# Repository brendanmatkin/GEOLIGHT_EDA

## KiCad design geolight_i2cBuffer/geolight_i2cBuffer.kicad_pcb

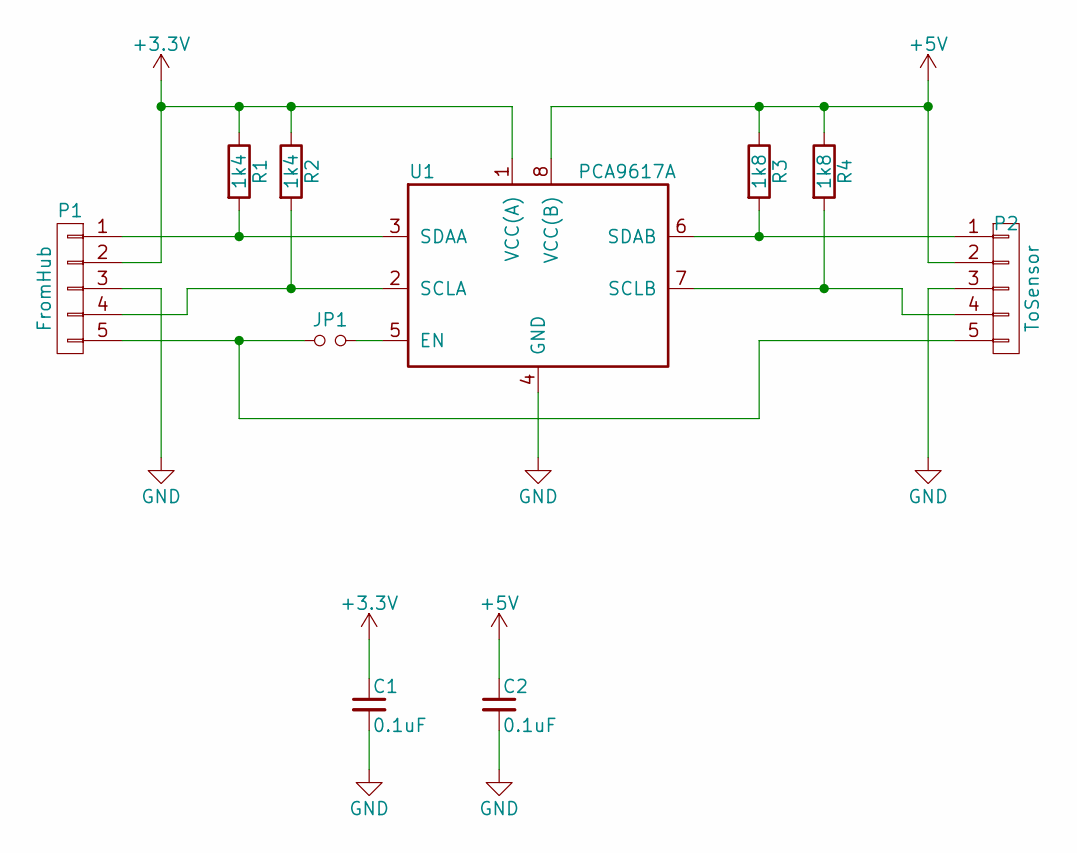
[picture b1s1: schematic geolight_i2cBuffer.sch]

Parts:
C1, C2: 0.1uF; C_Disc_D3_P2.5
JP1: Jumper_NO_Small; GS2
P1: FromHub; Pin_Header_Straight_1x05
P2: ToSensor; Socket_Strip_Straight_1x05
R1, R2: 1k4; R4
R3, R4: 1k8; R4
U1: PCA9617A; TSSOP-8_3x3mm_Pitch0.65mm

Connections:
+3V3: C1.1, P1.2, R1.1, R2.1, U1.1 (VCC(A))
+5V: C2.1, P2.2, R3.1, R4.1, U1.8 (VCC(B))
GND: C1.2, C2.2, P1.3, P2.3, U1.4 (GND)
unnamed 3: JP1.1, P1.5, P2.5; also elsewhere on the board
unnamed 4: JP1.2, U1.5 (EN); also elsewhere on the board
unnamed: P1.1, R1.2, U1.3 (SDAA)
unnamed: P1.4, R2.2, U1.2 (SCLA)
unnamed: P2.1, R3.2, U1.6 (SDAB)
unnamed: P2.4, R4.2, U1.7 (SCLB)

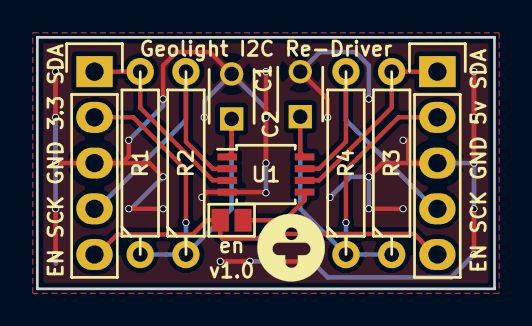
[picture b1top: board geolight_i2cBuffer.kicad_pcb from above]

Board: 2 copper layers, 25.4 x 14.0 mm, 10 parts (0 on the bottom side), 9 nets.

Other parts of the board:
en: Jumper_NO_Small; GS2

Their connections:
unnamed 3: en.1; also elsewhere on the board
unnamed 4: en.2; also elsewhere on the board

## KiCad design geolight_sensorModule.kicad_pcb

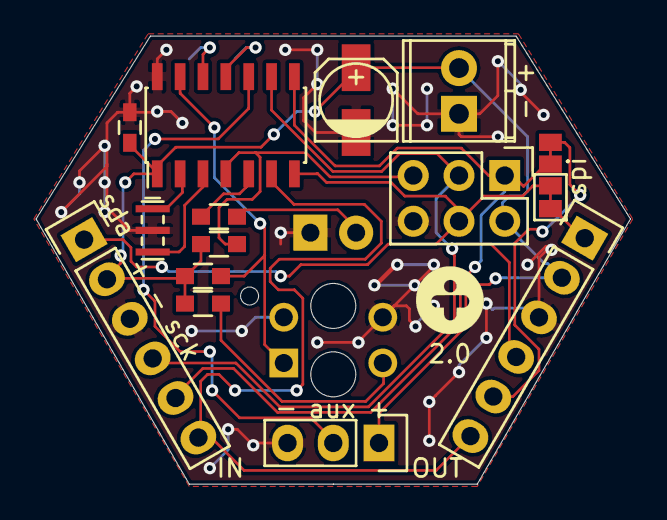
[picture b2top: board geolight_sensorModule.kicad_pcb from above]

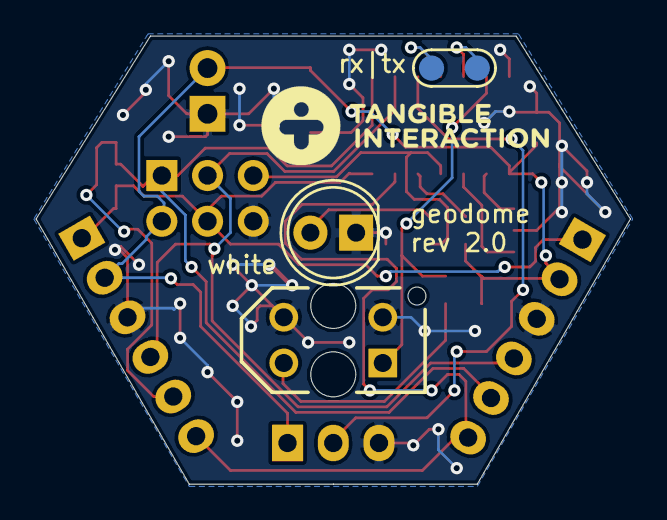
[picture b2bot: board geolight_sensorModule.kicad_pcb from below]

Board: 2 copper layers, 33.0 x 24.9 mm, 19 parts (3 on the bottom side), 16 nets.

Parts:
C2: 0.1uF; C_0603_HandSolderingShort
C3: 10uF; c_elec_4x5.8
IC1: ATTINY841-SSU; SOIC-14_3.9x8.7mm_Pitch1.27mm
IN: IN; Pin_Header_Straight_1x06
JP2, JP2#2: MISO_EN; Measurement_Point_Square-SMD-Pad_SmallRect
OUT: OUT; Pin_Header_Straight_1x06
P1: 5V inject; TerminalBlock_Pheonix_MPT-2.54mm_2pol
P2: OPEN; Pin_Header_Straight_2x03
P5: AUX Sensor; Pin_Header_Straight_1x03
P6: DEBUG; Test_Point
R1, R5: 220; R_0603_HandSolderingShort
R4, R6: 10k; R_0603_HandSolderingShort
U1: TCRT5000/L; XDCR_TCRT5000L
Y1: 16Mhz; Resonator_3.2x1.3mm
spi: I2C/SPI; GS2
white: White; LED-5MM

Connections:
+5V: C2.1, C3.1, IC1.1, IN.2, OUT.2, P1.2, P2.2, P5.1, R1.1, R4.1, R6.2
/AUX: IC1.10, P5.2
/MISO: IC1.8, IN.5, JP2.1, JP2#2.1, OUT.5, P2.1
/RESET: IC1.4, P2.5, R4.2
/RX: IC1.11, P6.2
/SCK/SCL: IC1.9, IN.4, OUT.4, P2.3
/SDA/MOSI: IC1.7, IN.1, OUT.1, P2.4, spi.1, spi.2
/SS: IC1.6, IN.6, OUT.6
/TX: IC1.12, P6.1
GND: C2.2, C3.2, IC1.14, IN.3, OUT.3, P1.1, P2.6, P5.3, U1.2, U1.3, Y1.2, white.1
unnamed: R5.1, white.2
unnamed: IC1.2, Y1.1
unnamed: IC1.3, Y1.3
unnamed: IC1.5, R5.2
unnamed: IC1.13, R6.1, U1.1
unnamed: R1.2, U1.4

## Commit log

2016-09-04 initial commit (first pass at schematic, footprints done, netlist exported, PCB started)
2016-09-04 removed 3rd, reversible jumper connector (difficult to mirror if reversible, probably not necessary to have 3)
2016-09-04 clean up schematic. Add SPI/I2C jumper.
2016-09-04 fixed mirrored in/out. updated netlist, footprints, PCB. Fixed UART test point rats nest
2016-09-06 minor changes.
2016-09-06 re-arranged PCB, routing done (all except ground plane)
2016-09-07 finished v0.99 (no top copper pour)
2016-09-07 v1.0! added top layer
2016-09-07 silkscreen changes
2016-09-07 RELEASE rev 1.0 (sent to elecrow)
2016-09-28 minor modifications? pre-rev2
2016-09-28 removed empty path cap, changed all 0603 to 0603_handsolder, fixed I2C wiring order, left SPI channels but most likely unused.
2016-09-28 90% complete for 8mm LED. Stopping for change back to 5mm.
2016-09-29 5mm, rev2 stage (wait a day and finalize)
2016-09-29 improved ground planes, revised labels/silk
2016-09-29 rev2 final staging probably (minor tweaks, fixed SPI option jumpers)
2016-09-29 rev2.0 outputs. No BOM yet, needs review before sending to manufacture
2017-08-22 the actual fabbed version including gerbers and BOM
